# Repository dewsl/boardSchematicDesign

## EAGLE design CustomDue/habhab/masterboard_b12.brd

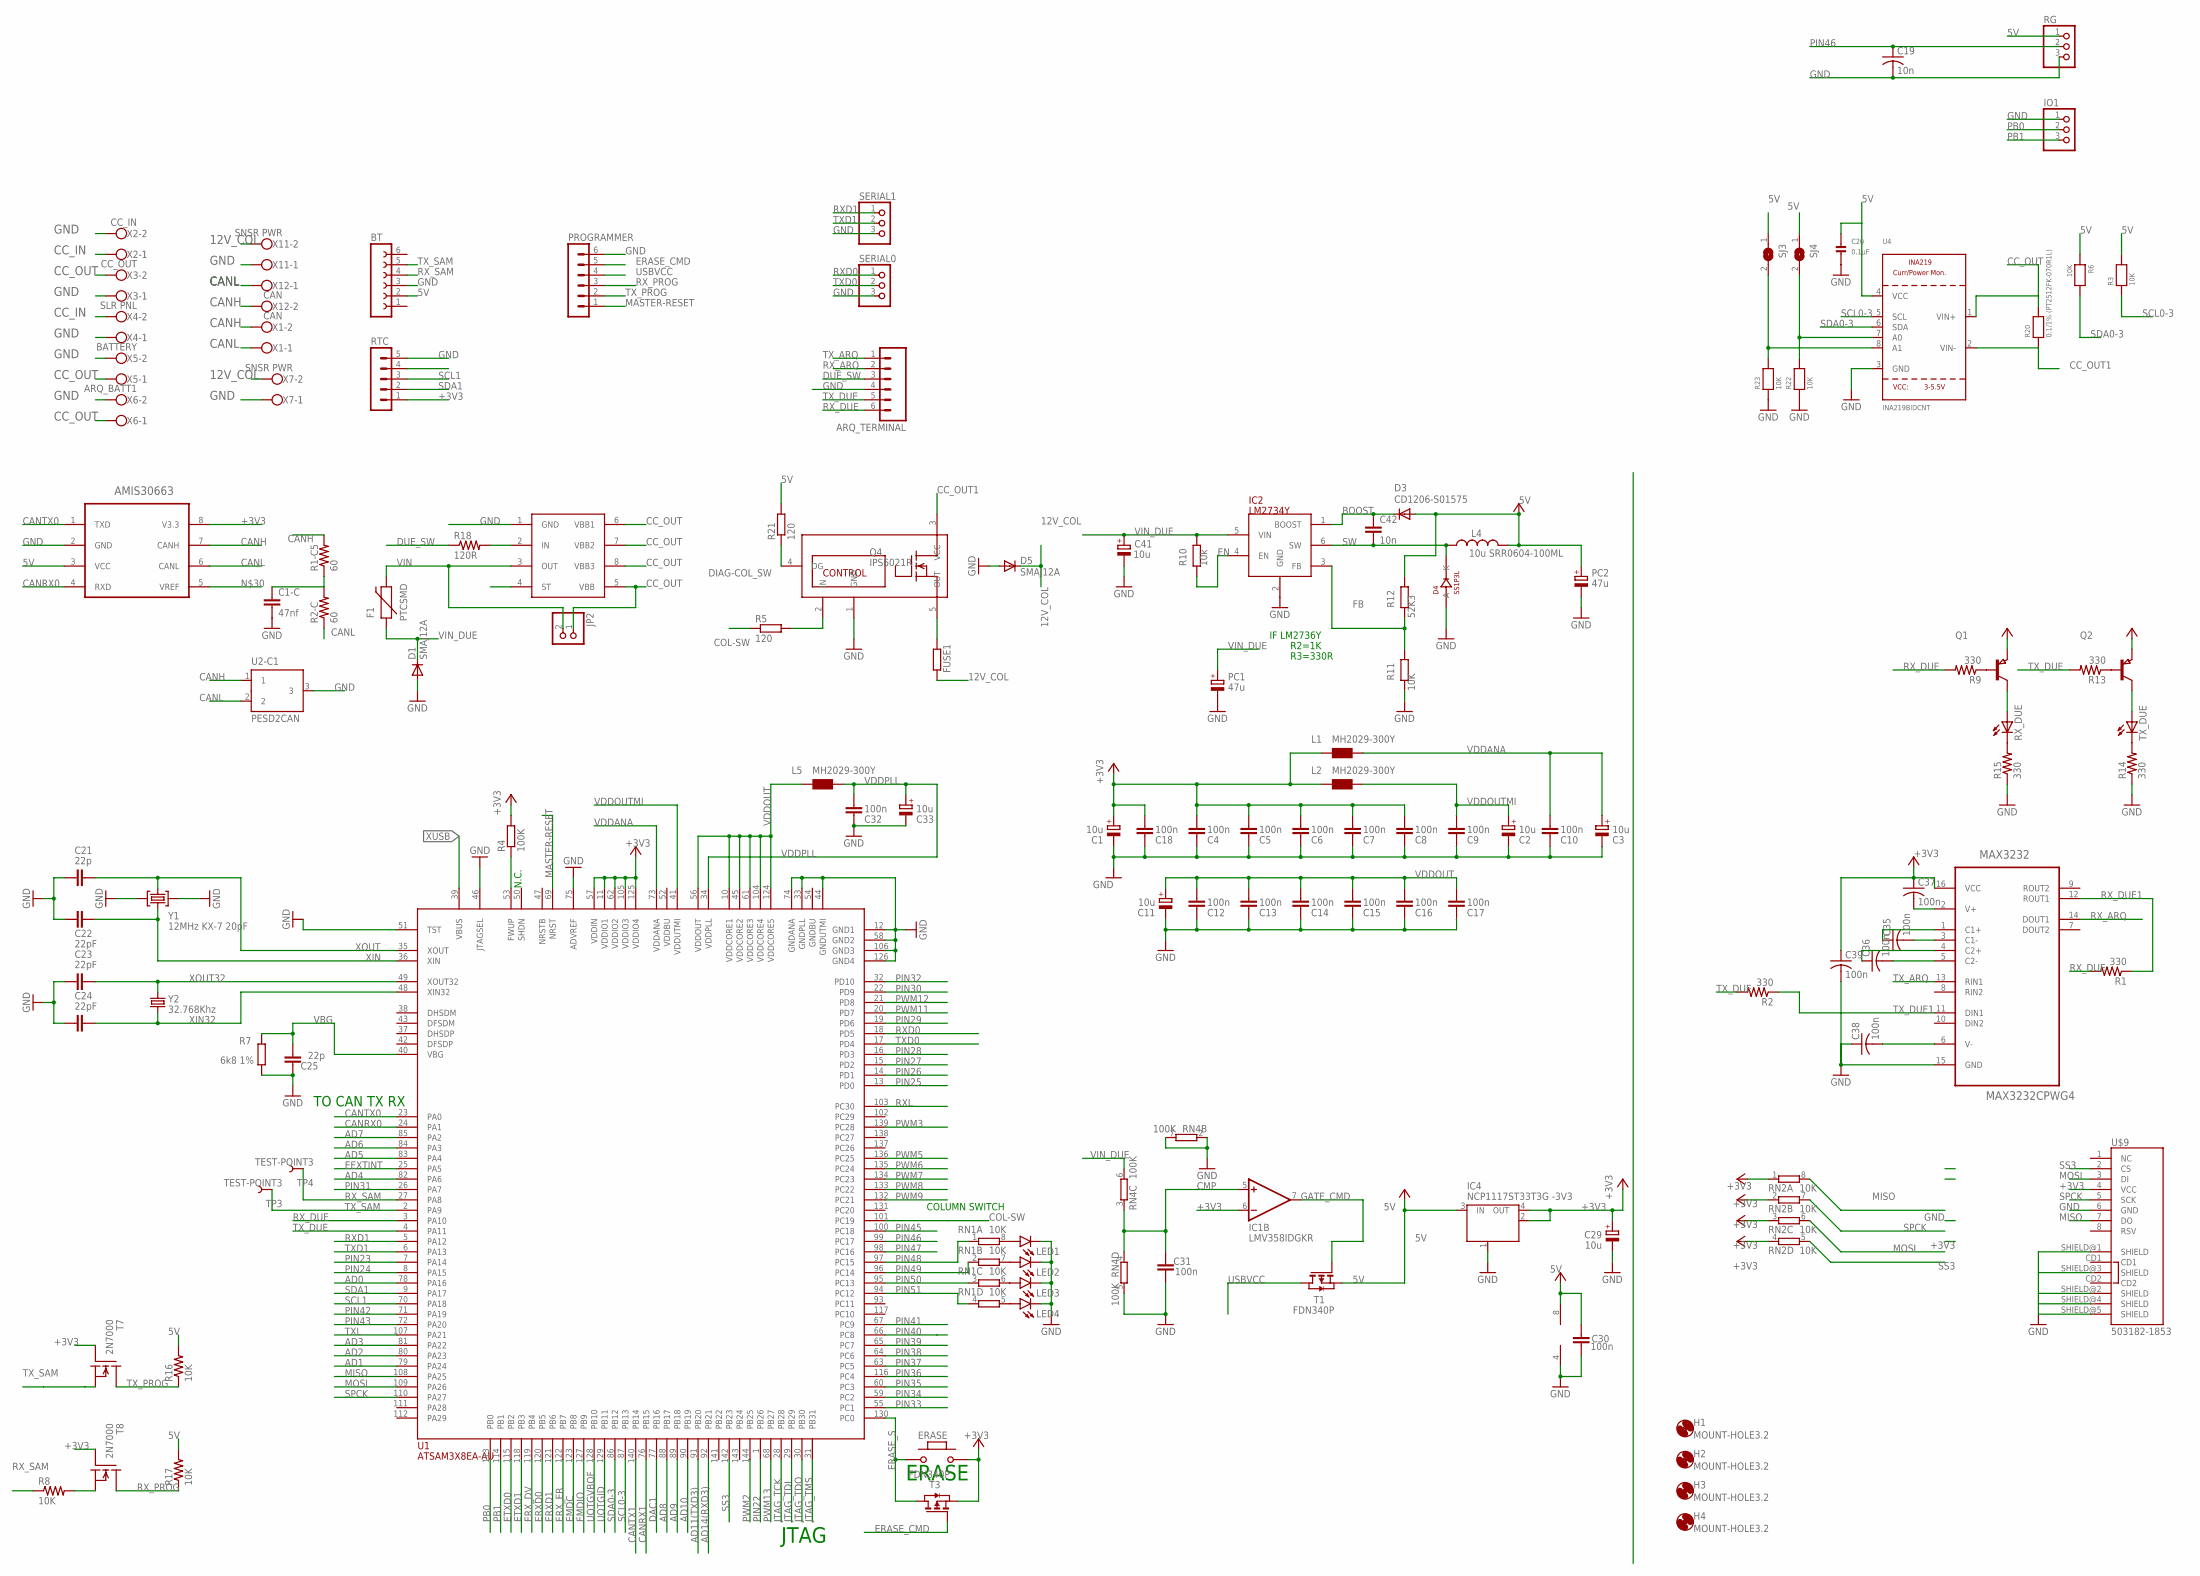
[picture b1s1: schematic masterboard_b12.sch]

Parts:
ARQ_TERMINAL: M06POLAR; MOLEX-1X6
BT: FE06-1; FE06
C1, C2, C3, C11, C29, C33, C41: 10u; SMC_B
C1-C: 47nf; C0805
C4, C5, C6, C7, C8, C9, C10, C12, C13, C14, C15, C16, C17, C18, C30, C31, C32: 100n; C0402
C19: 10n; C0603
C20: 0.1µF; 0603-MINI; MPN 04023C104KAT2A
C21, C25: 22p; C0402
C22, C23, C24: 22pF; C0402
C35, C36, C37, C38, C39: 100n; C0603
C42: 10n; C0603-ROUND
D1, D5: SMAJ12A; DO214AC
D3: CD1206-S01575; MINIMELF
D4: SS1P3L; DO220AAL
ERASE: MYSMD_PB157; SMD_157SW
F1: PTCSMD; PTC-1206
FUSE1: R-EU_1812X7R; 1812X7R
H1, H2, H3, H4: MOUNT-HOLE3.2; 3,2
IC1: LMV358IDGKR; MSOP08
IC2: LM2734Y; SOT23-6
IC4: NCP1117ST33T3G -3V3; SOT223
IO1: PINHD-1X3; 1X03
JP2: PINHD-1X2; 1X02
L1, L2, L5: MH2029-300Y; 0805
L4: 10u SRR0604-100ML; SRR0604
LED1, LED2, LED3, LED4: LED0603; LED-0603
MAX3232: MAX3232CPWG4; SOP65P640X120-16N
PC1, PC2: 47u; PANASONIC_D
PROGRAMMER: MA06-1
Q1, Q2: PNP-TRANSISTOR_SOT23; SOT23
Q4: IPS6021R; DPAK-5LEAD
R1, R2, R9, R13, R14, R15: 330; R0603
R1-C5, R2-C: 60; R2512
R3, R6, R22, R23: 10K; 0603-MINI; MPN TNPW040210K0BEED
R4: 100K; R0402
R5, R21: 120; R0603
R7: 6k8 1%; R0603-ROUND
R8, R16, R17: 10K; R0603
R10: 10k; R0402
R11: 10K; R0603-ROUND
R12: 52K3; R0603-ROUND
R18: 120R; R0603
R20: 0.1/1% (PT2512FK-070R1L); 2512
RG: PINHD-1X3; 1X03
RN1, RN2: 10K; CAT16
RN4: 100K; CAT16
RTC: MA05-1
RX_DUE: LEDCHIPLED_0603; CHIPLED_0603
SERIAL0, SERIAL1: PINHD-1X3; 1X03
SJ3, SJ4: SOLDERJUMPERREFLOW_NOPASTE; SOLDERJUMPER_REFLOW_NOPASTE
T1, T3: FDN340P; SOT-23
T7, T8: 2N7000; SOT23
TP3, TP4: TEST-POINT3; PAD.03X.03
TX_DUE: LEDCHIPLED_0603; CHIPLED_0603
U1: ATSAM3X8EA-AU; LQFP144
U2: INF-PG-DSO-8-24_L_1; INF-PG-DSO-8-24_L_1PRIMARY
U2-C: AMIS30663CAN; SOIC8
U2-C1: PESD2CAN; SOT23
U4: INA219BIDCNT; SOT23-8; MPN INA219BIDCNT
U$9: 503182-1853
X1, X12: CAN; W237-102
X2: CC_IN; W237-102
X3: CC_OUT; W237-102
X4: SLR PNL; W237-102
X5: BATTERY; W237-102
X6: ARQ_BATT1; W237-102
X7, X11: SNSR PWR; W237-102
Y1: 12MHz KX-7 20pF; CRYSTAL-3.2-2.5
Y2: 32.768Khz; RESONATOR_EPSON_FC_145

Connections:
5V: BT.2, C20.1, C30.2, D3.A, IC1.8 (V+), IC4.3 (IN), L4.P$2 (2), PC2.+, R3.2, R6.1, R12.1, R16.2, R17.2, R21.2, RG.1, SJ3.1, SJ4.1, T1.2 (S), U2-C.3 (VCC), U4.4 (VCC)
12V_COL: D5.C, FUSE1.2, X7.2, X11.2
+3V3: C1.+, C4.2, C5.2, C6.2, C7.2, C8.2, C18.2, C29.+, C37.1, C39.1, ERASE.1, IC1.6 (-IN), IC4.2 (OUT), IC4.4 (OUT), L1.1, L2.1, MAX3232.16 (VCC), Q1.2 (E), Q2.2 (E), R4.2, RN2.1, RN2.2 (1), RN2.3 (1), RN2.4 (1), RTC.1, T3.2 (S), T7.1 (G), T8.1 (G), U1.11 (VDDIO1), U1.57 (VDDIN), U1.62 (VDDIO2), U1.105 (VDDIO3), U1.125 (VDDIO4), U2-C.8 (V3.3), U$9.4 (VCC)
AD0: U1.78 (PA16)
AD1: U1.79 (PA24)
AD2: U1.80 (PA23)
AD3: U1.81 (PA22)
AD4: U1.82 (PA6)
AD5: U1.83 (PA4)
AD6: U1.84 (PA3)
AD7: U1.85 (PA2)
AD8: U1.88 (PB17)
AD9: U1.89 (PB18)
AD10: U1.90 (PB19)
AD11(TXD3): U1.91 (PB20)
AD14(RXD3): U1.92 (PB21)
BOOST: C42.1, D3.C, IC2.1 (BOOST)
CANH: R1-C5.2, U2-C.7 (CANH), U2-C1.1, X1.2, X12.2
CANL: R2-C.1, U2-C.6 (CANL), U2-C1.2, X1.1, X12.1
CANRX0: U1.24 (PA1), U2-C.4 (RXD)
CANRX1: U1.76 (PB15)
CANTX0: U1.23 (PA0), U2-C.1 (TXD)
CANTX1: U1.140 (PB14)
CC_IN: X2.1, X4.2
CC_OUT: JP2.1, R20.2, U2.5 (VBB), U2.6 (VBB1), U2.7 (VBB2), U2.8 (VBB3), U4.1 (VIN+), X3.2, X5.1, X6.1
CC_OUT1: Q4.3 (VCC), R20.1, U4.2 (VIN-)
CMP: C31.2, IC1.5 (+IN), RN4.3 (1), RN4.4 (1)
COL-SW: R5.1, U1.101 (PC19)
DAC1: U1.77 (PB16)
DIAG-COL_SW: Q4.4 (DG), R21.1
DUE_SW: ARQ_TERMINAL.3, R18.1
EEXTINT: U1.25 (PA5)
EMDC: U1.123 (PB8)
EMDIO: U1.127 (PB9)
EN: IC2.4 (EN), R10.2
ERASE_CMD: PROGRAMMER.5, T3.3 (G)
ERASE_S: ERASE.2, T3.1 (D), U1.130 (PC0)
ERXD0: U1.120 (PB5)
ERXD1: U1.121 (PB6)
ERX_DV: U1.119 (PB4)
ERX_ER: U1.122 (PB7)
ETXD0: U1.115 (PB2)
ETXD1: U1.118 (PB3)
FB: IC2.3 (FB), R11.1, R12.2
GATE_CMD: IC1.7 (OUT), T1.3 (G)
GND: ARQ_TERMINAL.4, BT.3, C1.-, C1-C.2, C2.-, C3.-, C4.1, C5.1, C6.1, C7.1, C8.1, C9.1, C10.1, C11.-, C12.1, C13.1, C14.1, C15.1, C16.1, C17.1, C18.1, C19.2, C20.2, C21.2, C22.2, C23.2, C24.2, C25.2, C29.-, C30.1, C31.1, C32.1, C33.-, C38.1, C39.2, C41.-, D1.A, D4.P$2 (A), D5.A, IC1.4 (V-), IC2.2 (GND), IC4.1 (GND/ADJ), IO1.1, LED1.C, LED2.C, LED3.C, LED4.C, MAX3232.15 (GND), PC1.-, PC2.-, PROGRAMMER.6, Q4.1 (GND), R7.1, R11.2, R14.1, R15.1, R22.1, R23.1, RG.3, RN4.2 (1), RN4.5 (2), RN4.7 (2), RTC.5, SERIAL0.3, SERIAL1.3, U1.12 (GND1), U1.33 (GNDPLL), U1.44 (GNDUTMI), U1.46 (JTAGSEL), U1.51 (TST), U1.58 (GND2), U1.74 (GNDANA), U1.75 (ADVREF), U1.106 (GND3), U1.126 (GND4), U2.1 (GND), U2-C.2 (GND), U2-C1.3, U4.3 (GND), U$9.6 (GND), U$9.SHIELD@1 (SHIELD), U$9.SHIELD@2 (SHIELD), U$9.SHIELD@3 (SHIELD), U$9.SHIELD@4 (SHIELD), U$9.SHIELD@5 (SHIELD), X2.2, X3.1, X4.1, X5.2, X6.2, X7.1, X11.1, Y1.2 (GND), Y1.4 (GND)
GNDBU: U1.54 (GNDBU)
JTAG_TCK: U1.28 (PB28)
JTAG_TDI: U1.29 (PB29)
JTAG_TDO: U1.30 (PB30)
JTAG_TMS: U1.31 (PB31)
MASTER-RESET: PROGRAMMER.1, U1.69 (NRST)
MISO: RN2.8 (2), U1.108 (PA25), U$9.7 (DO)
MOSI: RN2.6 (2), U1.109 (PA26), U$9.3 (DI)
unnamed: Q2.3 (C), TX_DUE.A
unnamed: FUSE1.1, Q4.5 (OUT)
unnamed: LED3.A, RN1.6 (2)
unnamed: R4.1, U1.53 (FWUP)
unnamed: Q1.1 (B), R9.1
unnamed: Q1.3 (C), RX_DUE.A
unnamed: R14.2, TX_DUE.C
unnamed: Q4.2 (IN), R5.2
unnamed: R8.2, T8.2 (S)
unnamed: C35.1, MAX3232.1 (C1+)
unnamed: C35.2, MAX3232.3 (C1-)
unnamed: C36.1, MAX3232.4 (C2+)
unnamed: C36.2, MAX3232.5 (C2-)
unnamed: R15.2, RX_DUE.C
unnamed: Q2.1 (B), R13.1
unnamed: C38.2, MAX3232.6 (V-)
unnamed: LED4.A, RN1.5 (2)
unnamed: C37.2, MAX3232.2 (V+)
unnamed: R18.2, U2.2 (IN)
unnamed: LED2.A, RN1.7 (2)
unnamed: LED1.A, RN1.8 (2)
unnamed: C1-C.1, R1-C5.1, R2-C.2
unnamed: R22.2, SJ4.2, U4.7 (A0)
unnamed: R23.2, SJ3.2, U4.8 (A1)
PB0: IO1.2, U1.113 (PB0)
PB1: IO1.3, U1.114 (PB1)
PIN22: U1.1 (PB26)
PIN23: U1.7 (PA14)
PIN24: U1.8 (PA15)
PIN25: U1.13 (PD0)
PIN26: U1.14 (PD1)
PIN27: U1.15 (PD2)
PIN28: U1.16 (PD3)
PIN29: U1.19 (PD6)
PIN30: U1.22 (PD9)
PIN31: U1.26 (PA7)
PIN32: U1.32 (PD10)
PIN33: U1.55 (PC1)
PIN34: U1.59 (PC2)
PIN35: U1.60 (PC3)
PIN36: U1.116 (PC4)
PIN37: U1.63 (PC5)
PIN38: U1.64 (PC6)
PIN39: U1.65 (PC7)
PIN40: U1.66 (PC8)
PIN41: U1.67 (PC9)
PIN42: U1.71 (PA19)
PIN43: U1.72 (PA20)
PIN45: U1.100 (PC18)
PIN46: C19.1, RG.2, U1.99 (PC17)
PIN47: U1.98 (PC16)
PIN48: RN1.1, U1.97 (PC15)
PIN49: RN1.2 (1), U1.96 (PC14)
PIN50: RN1.3 (1), U1.95 (PC13)
PIN51: RN1.4 (1), U1.94 (PC12)
PWM2: U1.144 (PB25)
PWM3: U1.139 (PC28)
PWM5: U1.136 (PC25)
PWM6: U1.135 (PC24)
PWM7: U1.134 (PC23)
PWM8: U1.133 (PC22)
PWM9: U1.132 (PC21)
PWM11: U1.20 (PD7)
PWM12: U1.21 (PD8)
PWM13: U1.68 (PB27)
RXD0: SERIAL0.1, U1.18 (PD5)
RXD1: SERIAL1.1, U1.5 (PA12)
RXL: U1.103 (PC30)
RX_ARQ: ARQ_TERMINAL.2, MAX3232.14 (DOUT1)
RX_DUE: ARQ_TERMINAL.6, R1.2, R9.2, U1.3 (PA10)
RX_DUE1: MAX3232.12 (ROUT1), R1.1
RX_PROG: PROGRAMMER.3, R17.1, T8.3 (D)
RX_SAM: BT.4, R8.1, TP4.P$1, U1.27 (PA8)
SCL0-3: R3.1, U1.87 (PB13), U4.5 (SCL)
SCL1: RTC.3, U1.70 (PA18)
SDA0-3: R6.2, U1.86 (PB12), U4.6 (SDA)
SDA1: RTC.2, U1.9 (PA17)
SPCK: RN2.7 (2), U1.110 (PA27), U$9.5 (SCK)
SS3: RN2.5 (2), U1.142 (PB23), U$9.2 (CS)
SW: C42.2, D4.P$1 (K), IC2.6 (SW), L4.P$1 (1)
TXD0: SERIAL0.2, U1.17 (PD4)
TXD1: SERIAL1.2, U1.6 (PA13)
TXL: U1.107 (PA21)
TX_ARQ: ARQ_TERMINAL.1, MAX3232.13 (RIN1)
TX_DUE: ARQ_TERMINAL.5, R2.2, R13.2, U1.4 (PA11)
TX_DUE1: MAX3232.11 (DIN1), R2.1
TX_PROG: PROGRAMMER.2, R16.1, T7.3 (D)
TX_SAM: BT.5, T7.2 (S), TP3.P$1, U1.2 (PA9)
UOTGID: U1.129 (PB11)
UOTGVBOF: U1.128 (PB10)
USBVCC: PROGRAMMER.4, T1.1 (D)
VBG: C25.1, R7.2, U1.40 (VBG)
VDDANA: C3.+, C10.2, L1.2, U1.73 (VDDANA)
VDDBU: U1.52 (VDDBU)
VDDOUT: C11.+, C12.2, C13.2, C14.2, C15.2, C16.2, C17.2, L5.1, U1.10 (VDDCORE1), U1.45 (VDDCORE2), U1.56 (VDDOUT), U1.61 (VDDCORE3), U1.104 (VDDCORE4), U1.124 (VDDCORE5)
VDDOUTMI: C2.+, C9.2, L2.2, U1.41 (VDDUTMI)
VDDPLL: C32.2, C33.+, L5.2, U1.34 (VDDPLL)
VIN: F1.2, JP2.2, U2.3 (OUT)
VIN_DUE: C41.+, D1.C, F1.1, IC2.5 (VIN), PC1.+, R10.1, RN4.6 (2)
XIN: C22.1, U1.36 (XIN), Y1.1 (C1)
XIN32: C24.1, U1.48 (XIN32), Y2.P$2 (2)
XOUT: C21.1, U1.35 (XOUT), Y1.3 (C2)
XOUT32: C23.1, U1.49 (XOUT32), Y2.P$1 (1)
XUSB: U1.39 (VBUS)

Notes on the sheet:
N.C.
JTAG
ERASE
IF LM2736Y
R2=1K
R3=330R
TO CAN TX RX
COLUMN SWITCH

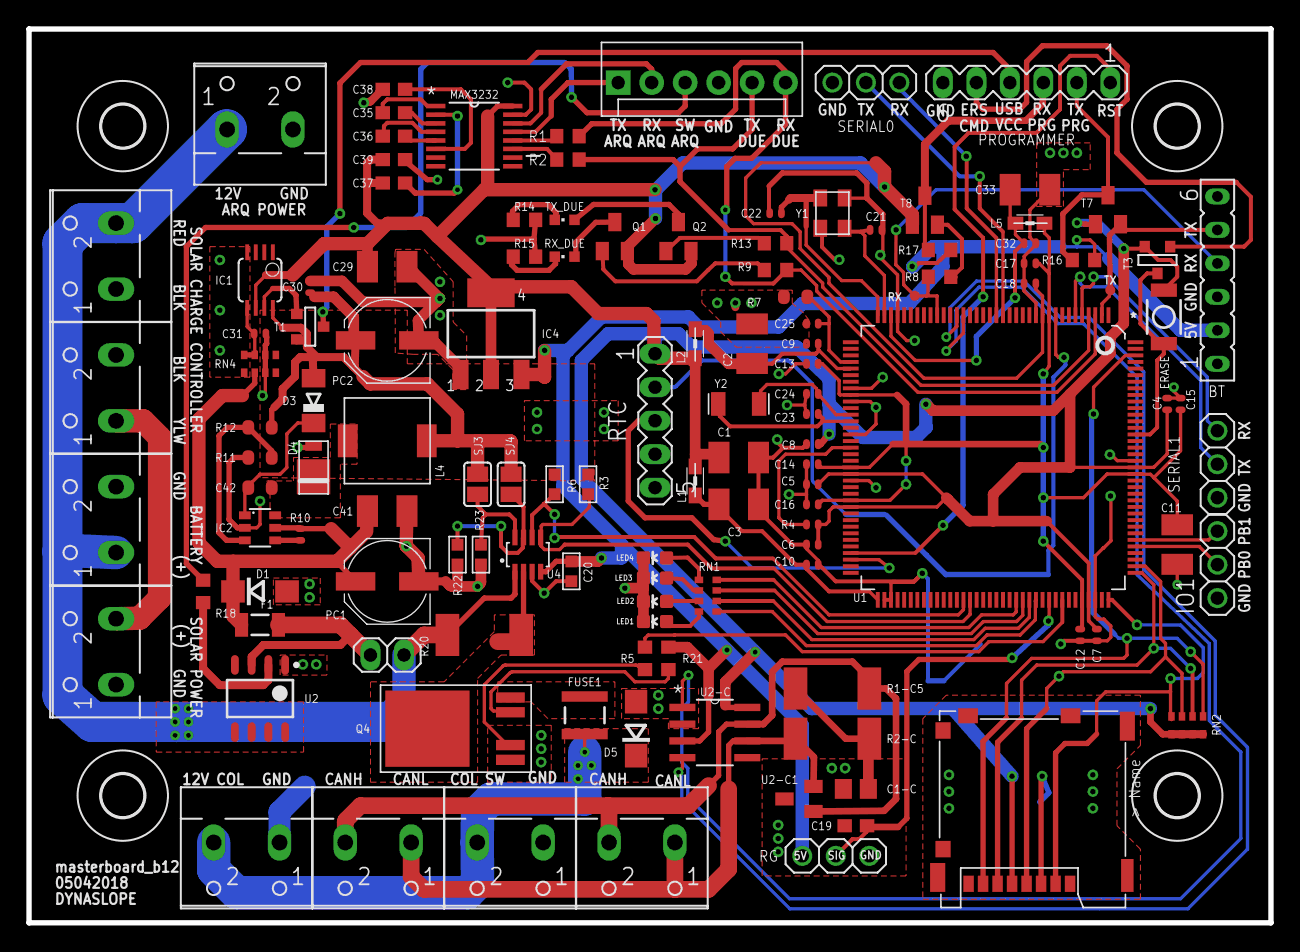
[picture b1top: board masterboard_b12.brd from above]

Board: 2 copper layers, 94.2 x 67.8 mm, 129 parts (0 on the bottom side), 88 nets.

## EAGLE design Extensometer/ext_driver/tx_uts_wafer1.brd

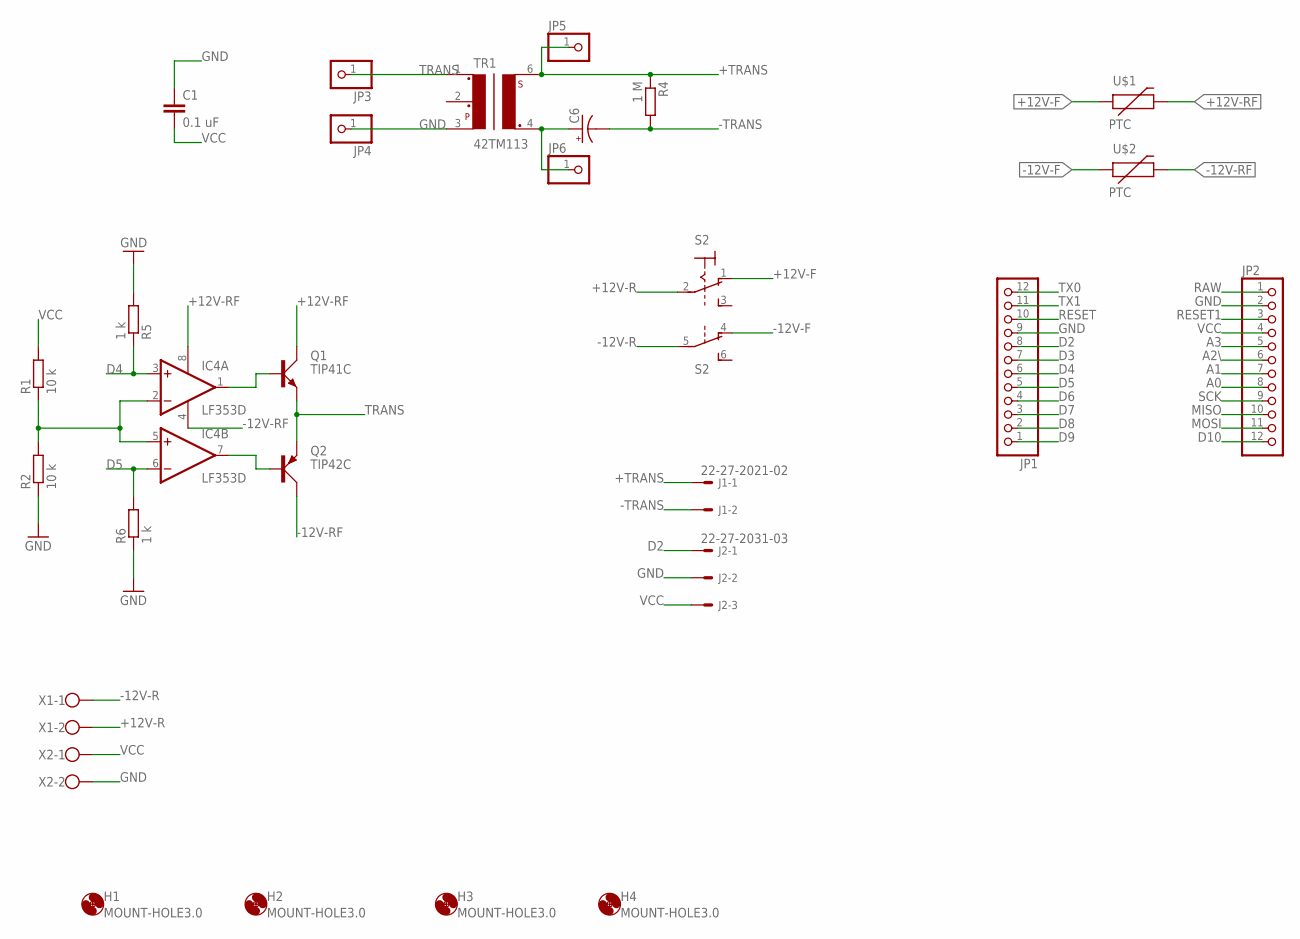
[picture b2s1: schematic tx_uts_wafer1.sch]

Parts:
C1: 0.1 uF; C0603
C6: CAP_POLC; PANASONIC_C
H1, H2, H3, H4: MOUNT-HOLE3.0; 3,0
IC4: LF353D; SO08
J1: 22-27-2021-02; 6410-02
J2: 22-27-2031-03; 6410-03
JP1, JP2: PINHD-1X12; 1X12
JP3, JP4, JP5, JP6: PINHD-1X1; 1X01
Q1: TIP41C; TO220AV
Q2: TIP42C; TO220AV
R1, R2: 10 k; R0603
R4: 1 M; R0603
R5, R6: 1 k; R0603
S2: M9040P2
TR1: 42TM113; 42TM
U$1, U$2: PTC; MC331XX
X1, X2: W237-102

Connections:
+12V-F: S2.1 (O), U$1.P$1 (1)
+12V-R: S2.2, X1.2
+12V-RF: IC4.8 (V+), Q1.C, U$1.P$2 (2)
+TRANS: J1.1, JP5.1, R4.1, TR1.6
-12V-F: S2.4 (O), U$2.P$1 (1)
-12V-R: S2.5, X1.1
-12V-RF: IC4.4 (V-), Q2.C, U$2.P$2 (2)
-TRANS: C6.-, J1.2, R4.2
A0: JP2.8
A1: JP2.7
A2\: JP2.6
A3: JP2.5
D2: J2.1, JP1.8
D3: JP1.7
D4: IC4.3 (+IN), JP1.6, R5.1
D5: IC4.6 (-IN), JP1.5, R6.2
D6: JP1.4
D7: JP1.3
D8: JP1.2
D9: JP1.1
D10: JP2.12
GND: C1.1, J2.2, JP1.9, JP2.2, JP4.1, R2.1, R5.2, R6.1, TR1.3, X2.2
MISO: JP2.10
MOSI: JP2.11
unnamed: IC4.7 (OUT), Q2.B
unnamed: IC4.1 (OUT), Q1.B
unnamed: C6.+, JP6.1, TR1.4
RAW: JP2.1
RESET: JP1.10
RESET1: JP2.3
SCK: JP2.9
TRANS: JP3.1, Q1.E, Q2.E, TR1.1
TX0: JP1.12
TX1: JP1.11
VCC: C1.2, J2.3, JP2.4, R1.2, X2.1
VREF: IC4.2 (-IN), IC4.5 (+IN), R1.1, R2.2

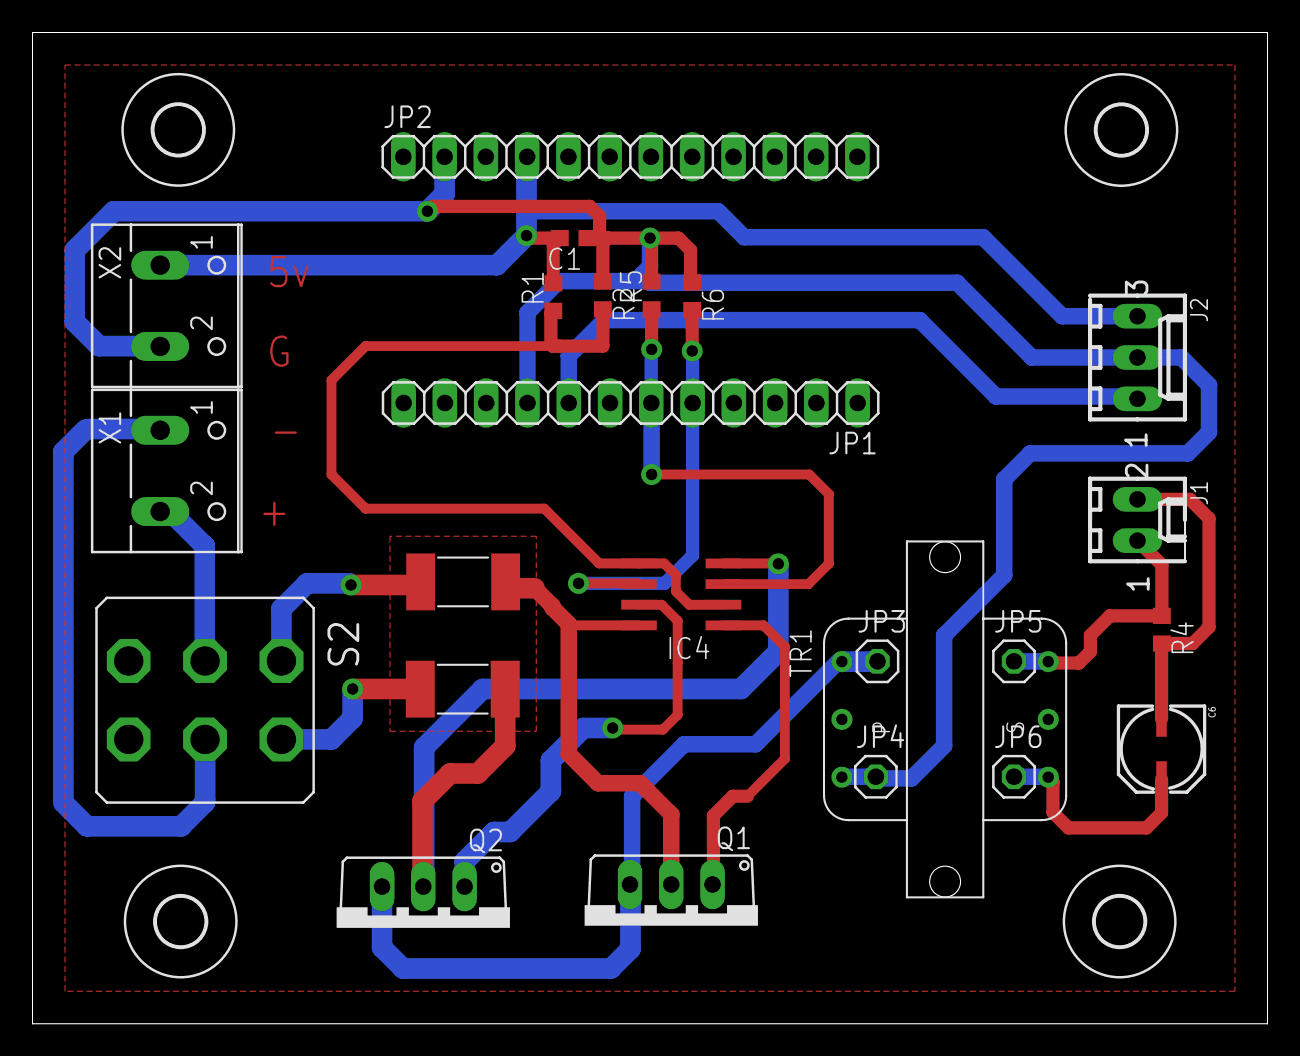
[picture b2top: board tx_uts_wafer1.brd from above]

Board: 2 copper layers, 76.0 x 61.0 mm, 28 parts (0 on the bottom side), 18 nets.

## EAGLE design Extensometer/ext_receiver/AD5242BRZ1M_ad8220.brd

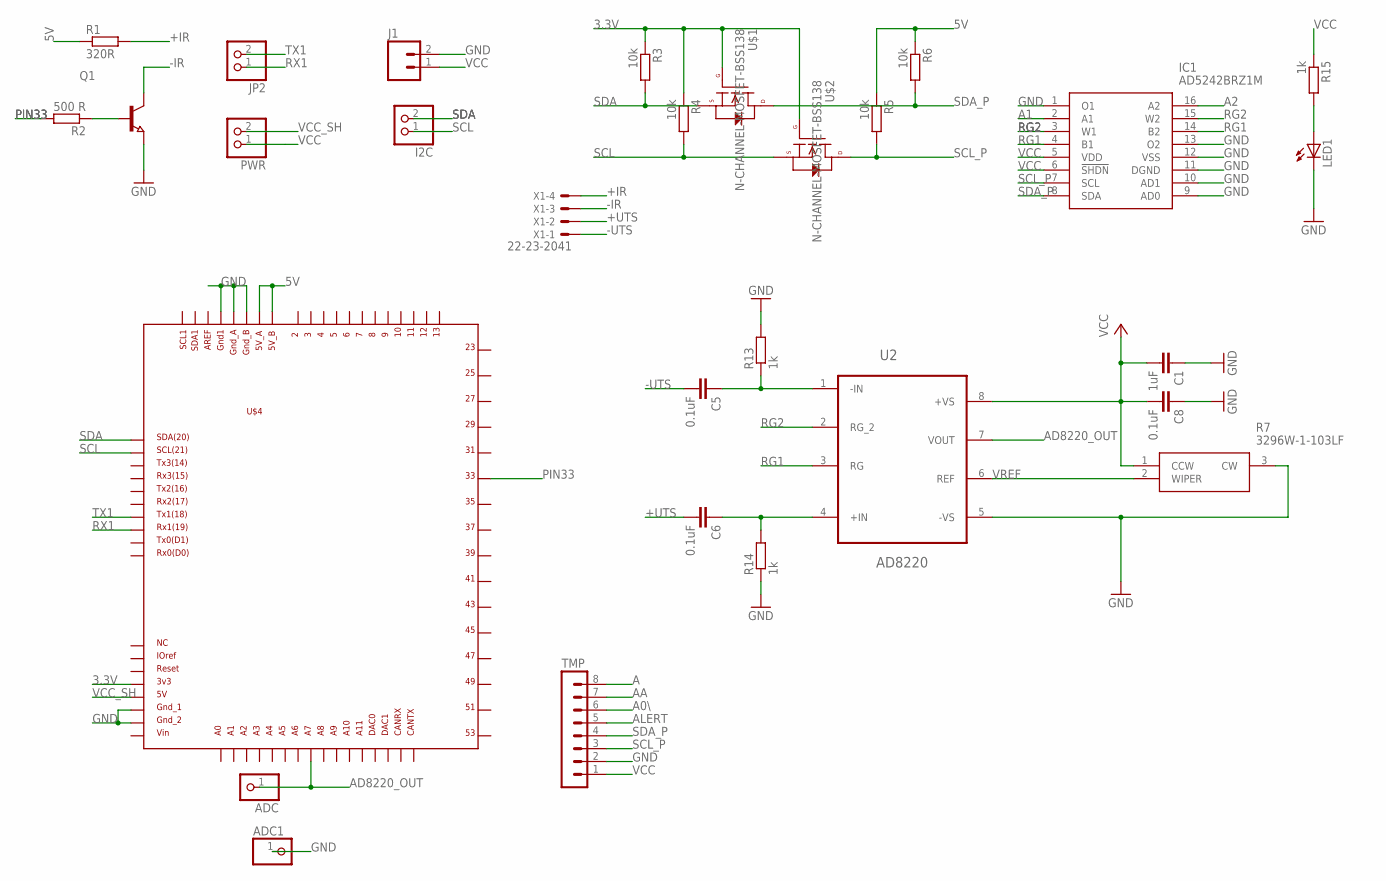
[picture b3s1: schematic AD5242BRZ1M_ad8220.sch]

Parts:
ADC, ADC1: PINHD-1X1; 1X01
C1: 1uF; C0603
C5, C6, C8: 0.1uF; C0603
I2C: PINHD-1X2; 1X02
IC1: AD5242BRZ1M; SOIC127P600X175-16N
J1: M02POLAR_LOCK; MOLEX-1X2_LOCK
JP2: PINHD-1X2; 1X02
LED1: LED_E; LED_1206
PWR: PINHD-1X2; 1X02
Q1: NPN-TRANSISTOR_SOT23; SOT23
R1: 320R; R0603
R2: 500 R; R0603
R3, R4, R5, R6: 10k; R0603
R7: 3296W-1-103LF; SHDR3W54P0X254_1X3_953X483X115
R13, R14, R15: 1k; R0603
TMP: MA08-1
U2: AD8220; SOP65P490X110-8N
U$1, U$2: N-CHANNEL-MOSFET-BSS138; SOT23-3
U$4: DUE_MAD
X1: 22-23-2041

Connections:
3.3V: R3.1, R4.1, U$1.1 (G), U$2.1 (G), U$4.3V3
5V: R1.1, R5.1, R6.1, U$4.5V_A, U$4.5V_B
+IN: C6.1, R14.2, U2.4 (+IN)
+IR: R1.2, X1.4
+UTS: C6.2, X1.2
-IN: C5.1, R13.1, U2.1 (-IN)
-IR: Q1.3 (C), X1.3
-UTS: C5.2, X1.1
A: TMP.8
A0\: TMP.6
A1: IC1.2 (A1)
A2: IC1.16 (A2)
AA: TMP.7
AD8220_OUT: ADC.1, U2.7 (VOUT), U$4.A7
ALERT: TMP.5
GND: ADC1.1, C1.1, C8.1, IC1.1 (O1), IC1.9 (AD0), IC1.10 (AD1), IC1.11 (DGND), IC1.12 (VSS), IC1.13 (O2), J1.2, LED1.C, Q1.2 (E), R7.3 (CW), R13.2, R14.1, TMP.2, U2.5 (-VS), U$4.GND1, U$4.GND_1, U$4.GND_2, U$4.GND_A, U$4.GND_B
unnamed: LED1.A, R15.2
unnamed: Q1.1 (B), R2.1
PIN33: R2.2, U$4.33
RG1: IC1.4 (B1), IC1.14 (B2), U2.3 (RG)
RG2: IC1.3 (W1), IC1.15 (W2), U2.2 (RG_2)
RX1: JP2.1, U$4.RX1
SCL: I2C.1, R4.2, U$2.2 (S), U$4.SCL
SCL_P: IC1.7 (SCL), R5.2, TMP.3, U$2.3 (D)
SDA: I2C.2, R3.2, U$1.2 (S), U$4.SDA
SDA_P: IC1.8 (SDA), R6.2, TMP.4, U$1.3 (D)
TX1: JP2.2, U$4.TX1
VCC: C1.2, C8.2, IC1.5 (VDD), IC1.6 (!SHDN), J1.1, PWR.1, R7.1 (CCW), R15.1, TMP.1, U2.8 (+VS)
VCC_SH: PWR.2, U$4.5V
VREF: R7.2 (WIPER), U2.6 (REF)

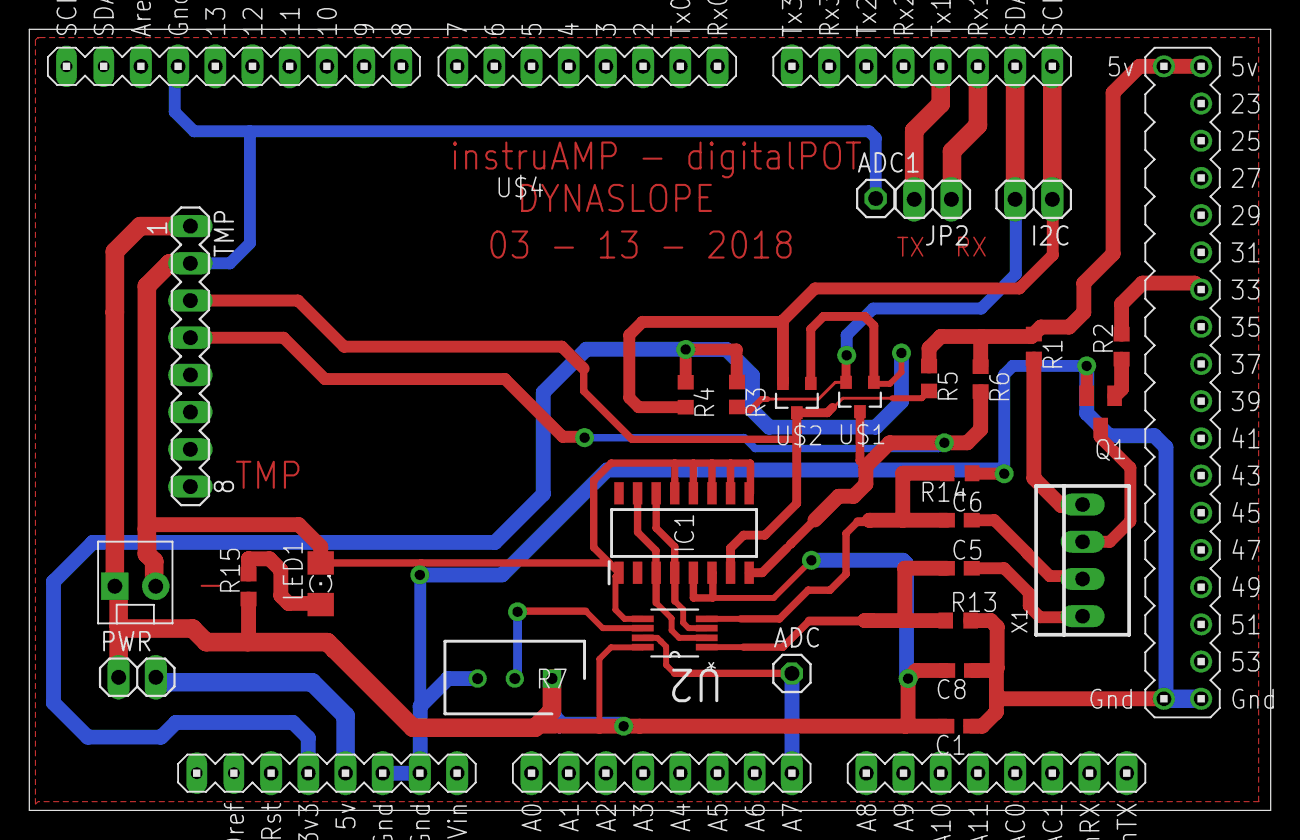
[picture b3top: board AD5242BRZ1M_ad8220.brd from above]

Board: 2 copper layers, 84.8 x 53.3 mm, 29 parts (0 on the bottom side), 24 nets.

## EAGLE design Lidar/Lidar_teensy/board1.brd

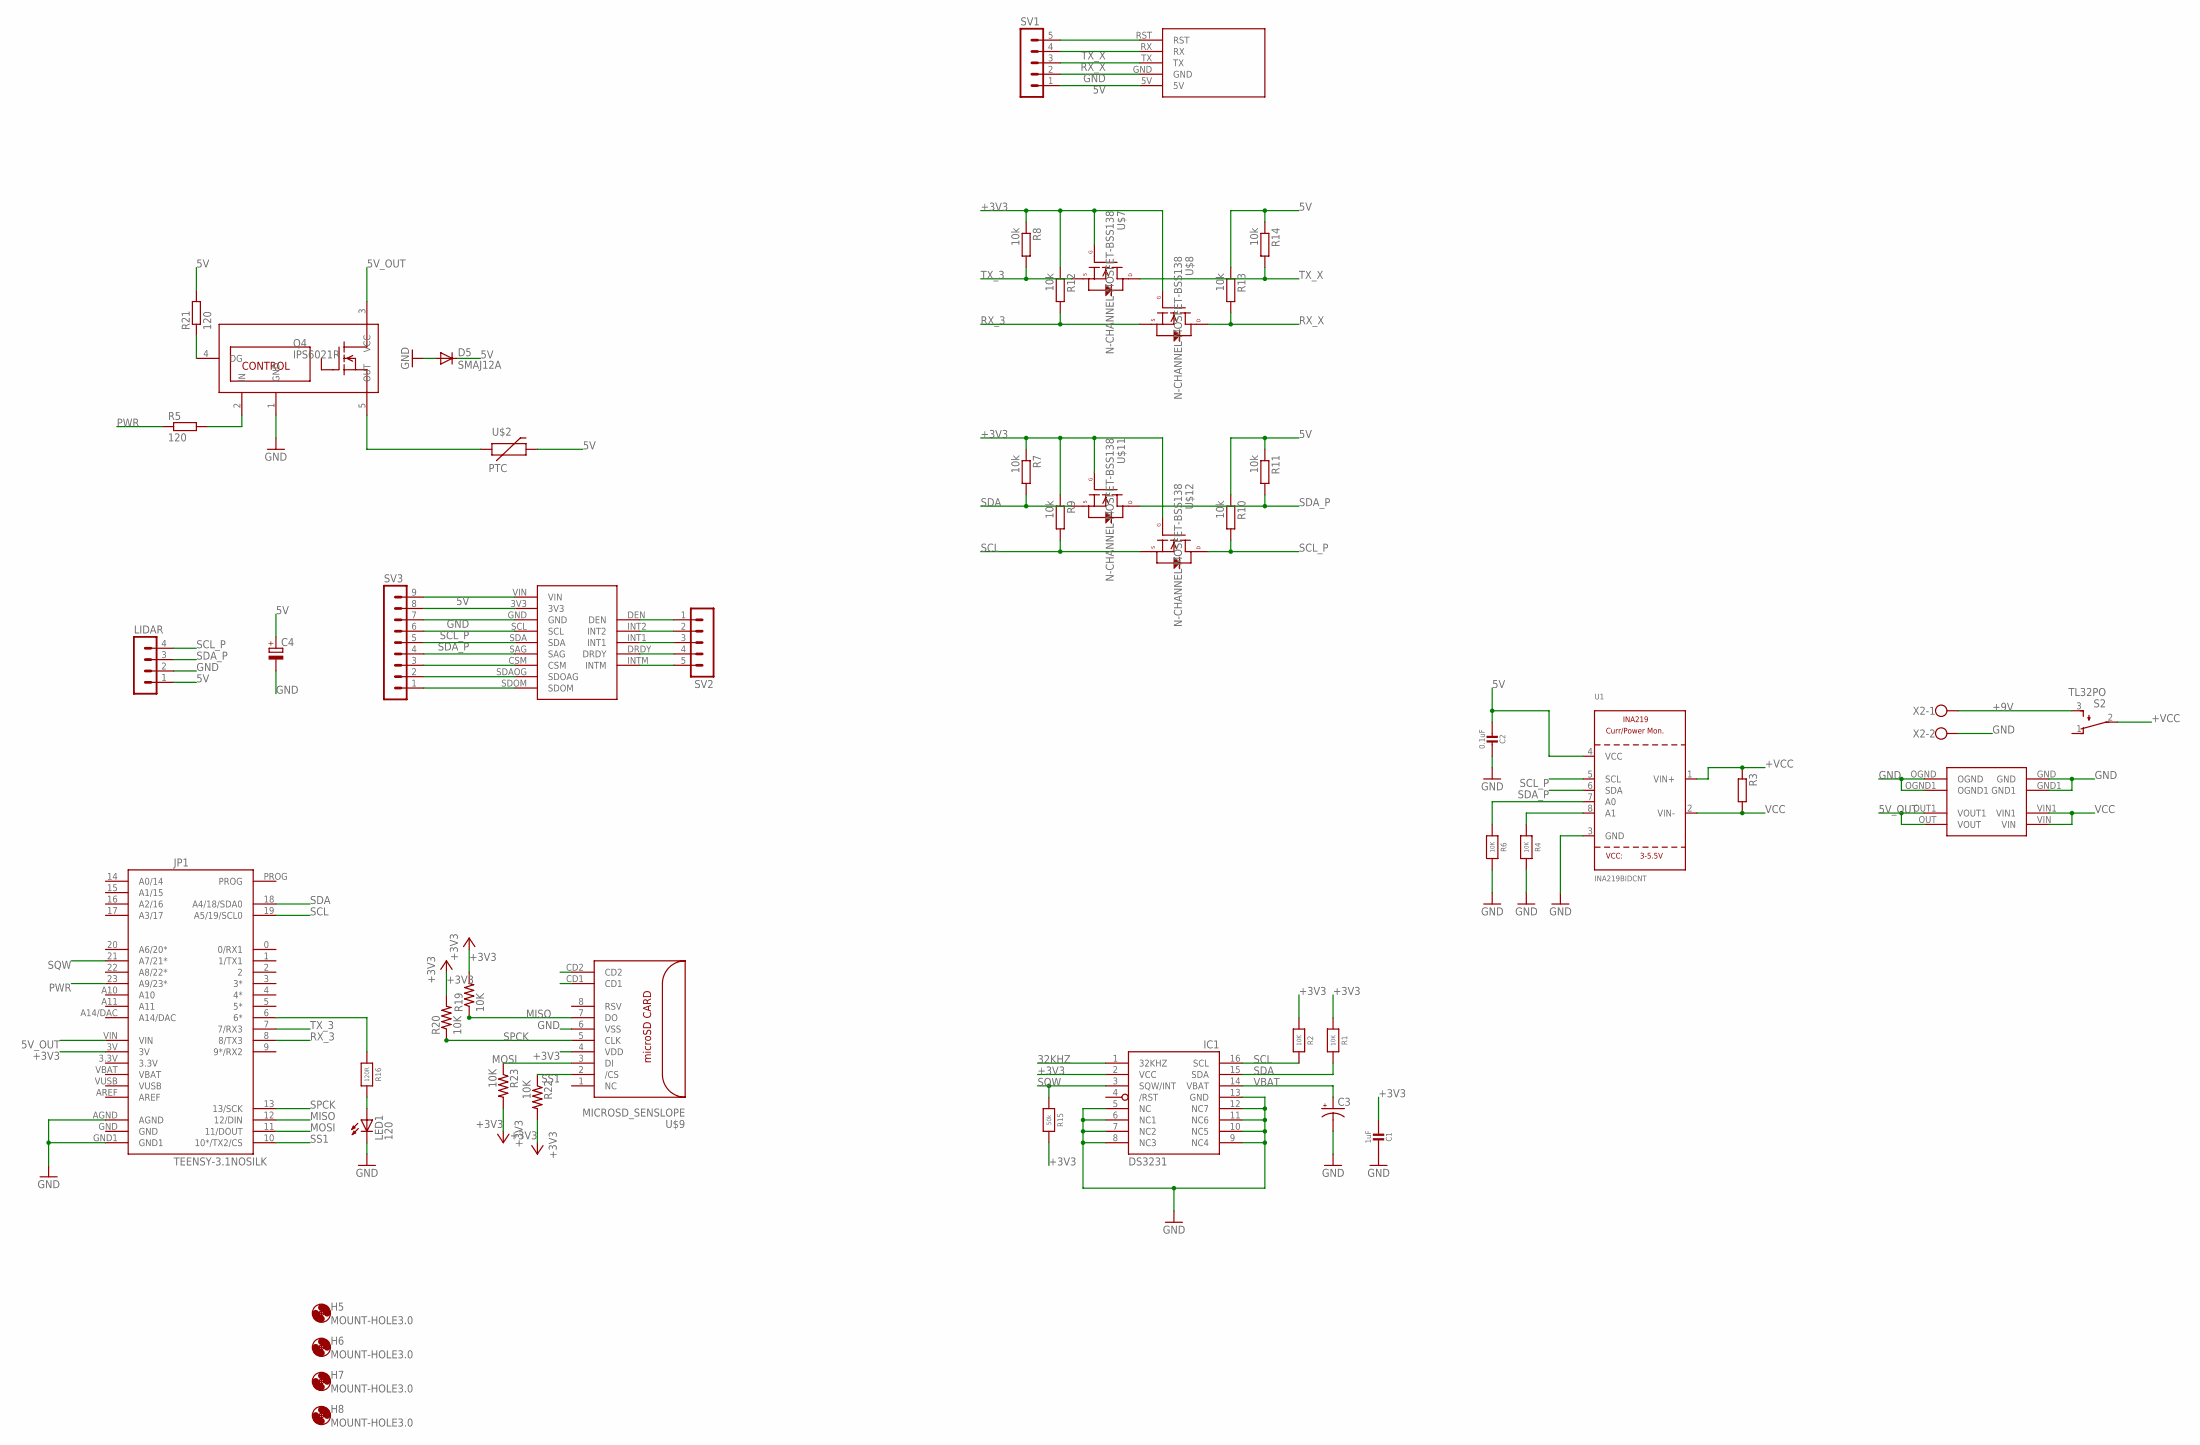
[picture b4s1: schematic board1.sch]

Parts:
C1: 1uF; 0805-NO
C2: 0.1uF; 0805-NO
C3: CAP_POL7343; EIA7343
C4: CPOL-EUG; PANASONIC_G
D5: SMAJ12A; DO214AC
H5, H6, H7, H8: MOUNT-HOLE3.0; 3,0
IC1: DS3231/SO; SO16W
JP1: TEENSY-3.1NOSILK; TEENSY-3.1_NOSILK
LED1: 120; CHIPLED_1206
LIDAR: MA04-1
Q4: IPS6021R; DPAK-5LEAD
R1, R2, R4, R6: 10K; 0805-NO
R3: RR2512; R2512
R5, R21: 120; R0603
R7, R8, R9, R10, R11, R12, R13, R14: 10k; R0603
R15: 50k; 0805-NO
R16: 120R; 0805-NO
R19, R20, R22, R23: 10K; R0603
S2: TL32PO; TL3XPO
SV1, SV2: MA05-1
SV3: MA09-1
U1: INA219BIDCNT; SOT23-8
U$1: LSM9DS1; 9DOF
U$2: PTC; MC331XX
U$3: DC-DC
U$7, U$8, U$11, U$12: N-CHANNEL-MOSFET-BSS138; SOT23-3
U$9: MICROSD_SENSLOPE; SENSLOPESD
X2: W237-102
XBEE: XBEE-SHIELD

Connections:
5V: C2.2, C4.+, D5.C, LIDAR.1, R10.1, R11.1, R13.1, R14.1, R21.2, SV1.1, SV3.9, U1.4 (VCC), U$1.VIN, U$2.P$2 (2), XBEE.5V
5V_OUT: JP1.VIN, Q4.3 (VCC), U$3.OUT (VOUT), U$3.OUT1 (VOUT1)
32KHZ: IC1.1 (32KHZ)
+3V3: C1.2, IC1.2 (VCC), JP1.3V, R1.1, R2.1, R7.1, R8.1, R9.1, R12.1, R15.2, R19.2, R20.2, R22.2, R23.2, U$7.1 (G), U$8.1 (G), U$9.4 (VDD), U$11.1 (G), U$12.1 (G)
+9V: S2.3 (S), X2.1
+VCC: R3.1, S2.2, U1.1 (VIN+)
CD: U$9.CD1
GND: C1.1, C2.1, C3.C (-), C4.-, D5.A, IC1.5 (NC), IC1.6 (NC1), IC1.7 (NC2), IC1.8 (NC3), IC1.9 (NC4), IC1.10 (NC5), IC1.11 (NC6), IC1.12 (NC7), IC1.13 (GND), JP1.AGND, JP1.GND1, LED1.C, LIDAR.2, Q4.1 (GND), R4.2, R6.2, SV1.2, SV3.7, U1.3 (GND), U$1.GND, U$3.GND, U$3.GND1, U$3.OGND, U$3.OGND1, U$9.6 (VSS), X2.2, XBEE.GND
MISO: JP1.12 (12/DIN), R19.1, U$9.7 (DO)
MOSI: JP1.11 (11/DOUT), R23.1, U$9.3 (DI)
unnamed: R4.1, U1.8 (A1)
unnamed: R6.1, U1.7 (A0)
unnamed: JP1.6 (6*), R16.1
unnamed: Q4.4 (DG), R21.1
unnamed: LED1.A, R16.2
unnamed: SV3.8, U$1.3V3
unnamed: Q4.2 (IN), R5.2
unnamed: SV3.4, U$1.SAG
unnamed: SV3.3, U$1.CSM
unnamed: SV3.2, U$1.SDAOG (SDOAG)
unnamed: Q4.5 (OUT), U$2.P$1 (1)
unnamed: SV3.1, U$1.SDOM
unnamed: SV2.1, U$1.DEN
unnamed: SV2.2, U$1.INT2
unnamed: SV2.3, U$1.INT1
unnamed: SV2.4, U$1.DRDY
unnamed: SV2.5, U$1.INTM
unnamed: SV1.5, XBEE.RST
PWR: JP1.23 (A9/23*), R5.1
RX_3: JP1.8 (8/TX3), R12.2, U$8.2 (S)
RX_X: R13.2, SV1.3, U$8.3 (D), XBEE.TX
SCL: IC1.16 (SCL), JP1.19 (A5/19/SCL0), R2.2, R9.2, U$12.2 (S)
SCL_P: LIDAR.4, R10.2, SV3.6, U1.5 (SCL), U$1.SCL, U$12.3 (D)
SDA: IC1.15 (SDA), JP1.18 (A4/18/SDA0), R1.2, R7.2, U$11.2 (S)
SDA_P: LIDAR.3, R11.2, SV3.5, U1.6 (SDA), U$1.SDA, U$11.3 (D)
SPCK: JP1.13 (13/SCK), R20.1, U$9.5 (CLK)
SQW: IC1.3 (SQW/INT), JP1.21 (A7/21*), R15.1
SS1: JP1.10 (10*/TX2/CS), R22.1, U$9.2 (/CS)
TX_3: JP1.7 (7/RX3), R8.2, U$7.2 (S)
TX_X: R14.2, SV1.4, U$7.3 (D), XBEE.RX
VBAT: C3.A (+), IC1.14 (VBAT)
VCC: R3.2, U1.2 (VIN-), U$3.VIN, U$3.VIN1

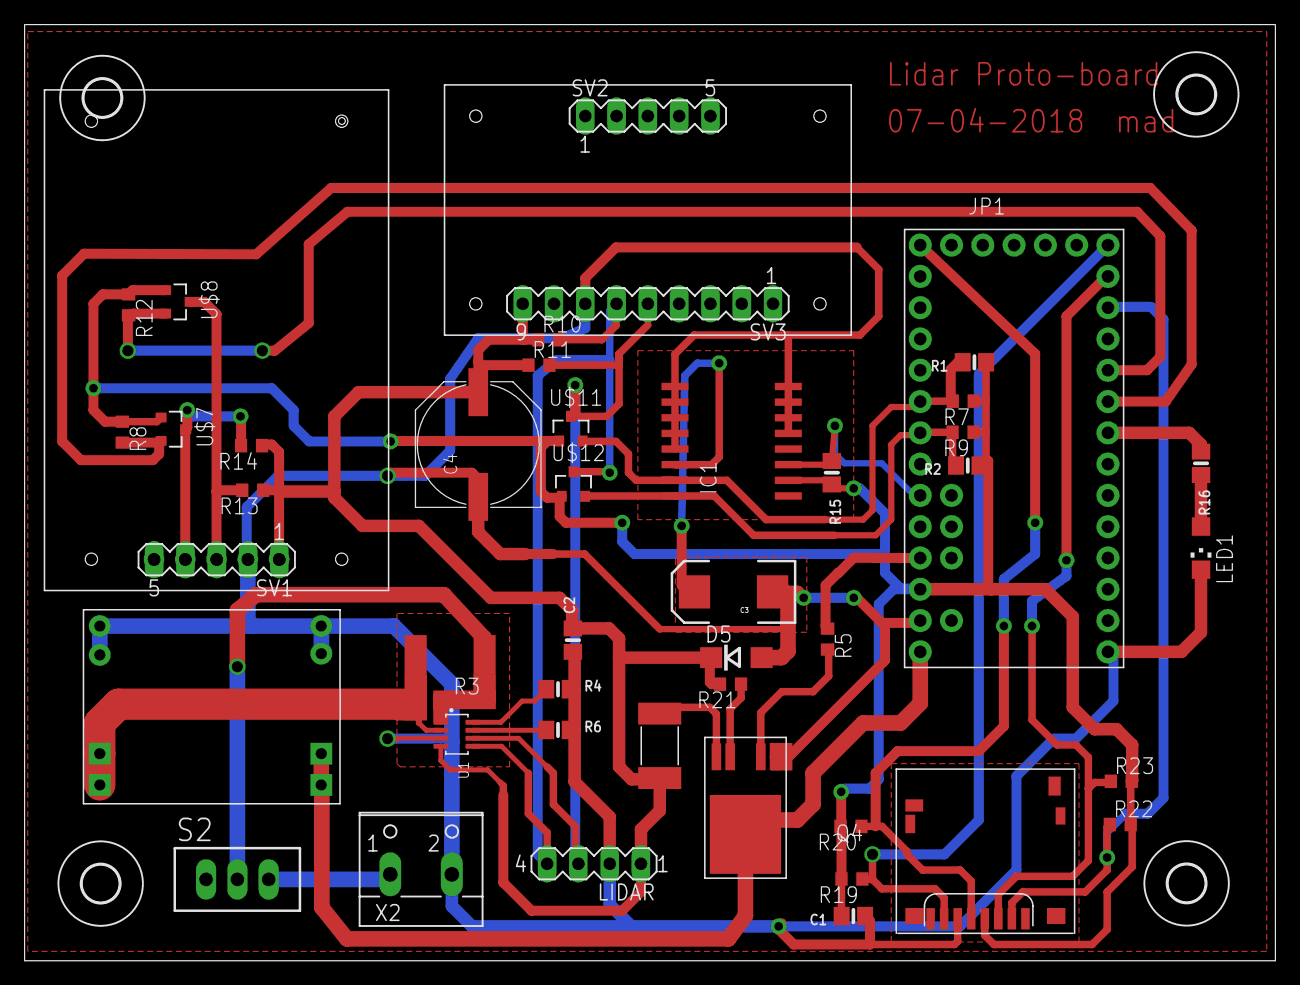
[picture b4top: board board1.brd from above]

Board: 2 copper layers, 101.5 x 76.0 mm, 50 parts (0 on the bottom side), 40 nets.

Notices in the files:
parts and their libraries:
SparkFun-PowerIC: Licensing: CC v3.0 Share-Alike You are welcome to use this library for commercial purposes.
SparkFun-Passives: Licensing: Creative Commons ShareAlike 4.0 International - https://creativecommons.org/licenses/by-sa/4.0
